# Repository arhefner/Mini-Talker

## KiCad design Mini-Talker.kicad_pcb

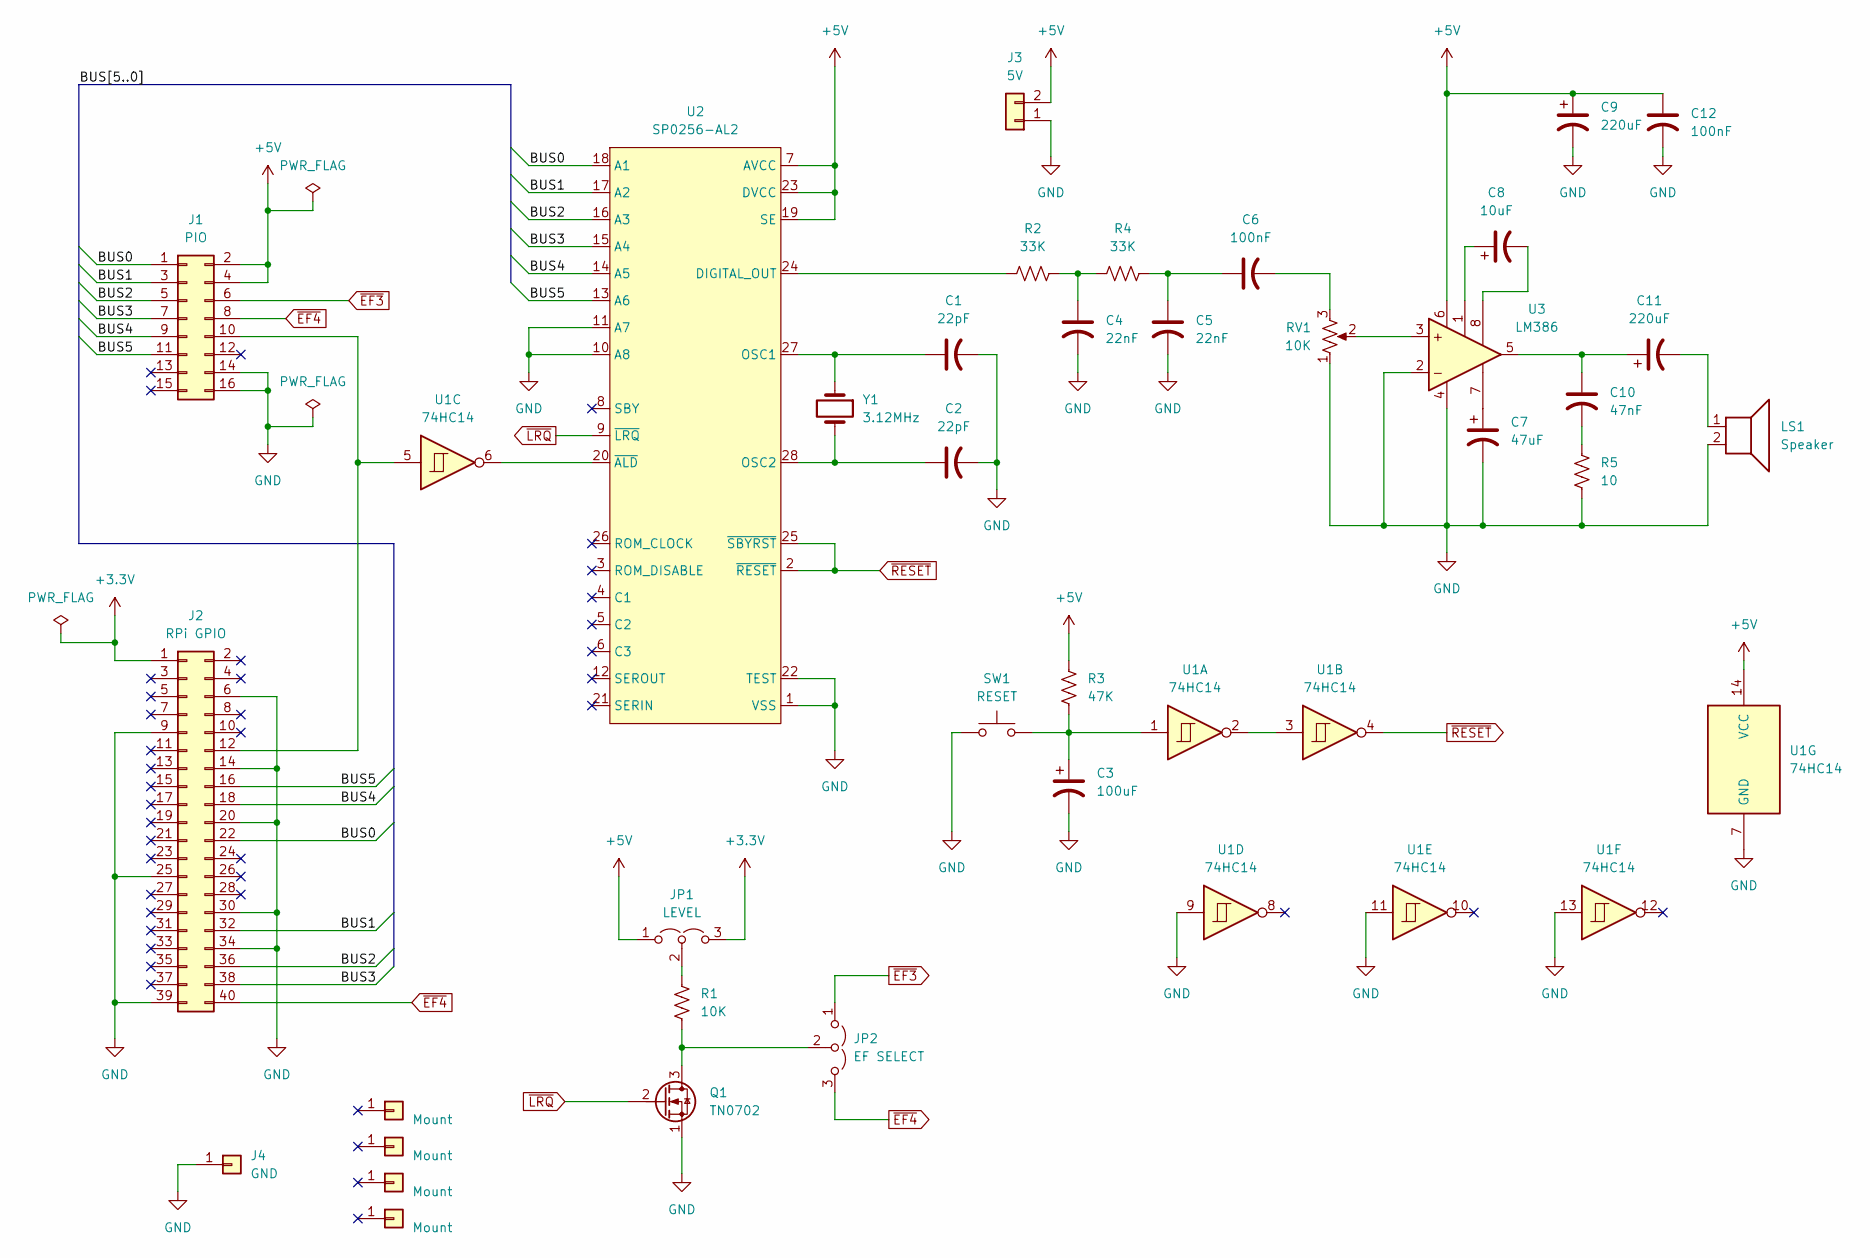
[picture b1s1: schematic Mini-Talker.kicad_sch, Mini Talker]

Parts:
C1, C2: 22pF; C_Disc_D5.0mm_W2.5mm_P2.50mm
C3: 100uF; CP_Radial_D5.0mm_P2.00mm
C4, C5: 22nF; C_Disc_D5.0mm_W2.5mm_P5.00mm
C6, C12: 100nF; C_Disc_D5.0mm_W2.5mm_P5.00mm
C7: 47uF; CP_Radial_D5.0mm_P2.00mm
C8: 10uF; CP_Radial_D4.0mm_P1.50mm
C9, C11: 220uF; CP_Radial_D6.3mm_P2.50mm
C10: 47nF; C_Disc_D5.0mm_W2.5mm_P5.00mm
J1: PIO; PinHeader_2x08_P2.54mm_Vertical
J2: RPi GPIO; PinHeader_2x20_P2.54mm_Vertical
J3: 5V; PinHeader_1x02_P2.54mm_Horizontal
J4: GND; SolderWire-0.75sqmm_1x01_D1.25mm_OD2.3mm
J5, J6, J7, J8: Mount; 1-Pin
JP1: LEVEL; PinHeader_1x03_P2.54mm_Vertical
JP2: EF SELECT; PinHeader_1x03_P2.54mm_Vertical
LS1: Speaker; TerminalBlock_Phoenix_MKDS-1,5-2-5.08_1x02_P5.08mm_Horizont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
Q1: TN0702; TO-92L
R1: 10K; R_Axial_DIN0207_L6.3mm_D2.5mm_P10.16mm_Horizontal
R2, R4: 33K; R_Axial_DIN0207_L6.3mm_D2.5mm_P10.16mm_Horizontal
R3: 47K; R_Axial_DIN0207_L6.3mm_D2.5mm_P10.16mm_Horizontal
R5: 10; R_Axial_DIN0207_L6.3mm_D2.5mm_P10.16mm_Horizontal
RV1: 10K; P160KN0QC20A10K
SW1: RESET; SW_PUSH_6mm_H4.3mm
U1: 74HC14; DIP-14_W7.62mm_Socket
U2: SP0256-AL2; DIP-28_W15.24mm_Socket
U3: LM386; DIP-8_W7.62mm_Socket
Y1: 3.12MHz; Crystal_HC49-U_Horizontal

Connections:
+3.3V: J2.1, JP1.3 (B)
+5V: C9.1, C12.1, J1.2, J1.4, J3.2, JP1.1 (A), R3.1, U1.14 (VCC), U2.7 (AVCC), U2.19 (SE), U2.23 (DVCC), U3.6 (V+)
/BUS0: J1.1, J2.22, U2.18 (A1)
/BUS1: J1.3, J2.32, U2.17 (A2)
/BUS2: J1.5, J2.36, U2.16 (A3)
/BUS3: J1.7, J2.38, U2.15 (A4)
/BUS4: J1.9, J2.18, U2.14 (A5)
/BUS5: J1.11, J2.16, U2.13 (A6)
GND: C1.2, C2.2, C3.2, C4.2, C5.2, C7.2, C9.2, C12.2, J1.14, J1.16, J2.6, J2.9, J2.14, J2.20, J2.25, J2.30, J2.34, J2.39, J3.1, J4.1, LS1.2, Q1.1 (S), R5.2, RV1.1, SW1.1, U1.7 (GND), U1.9, U1.11, U1.13, U2.1 (VSS), U2.10 (A8), U2.11 (A7), U2.22 (TEST), U3.2 (-), U3.4 (GND)
unnamed: C3.1, R3.2, SW1.2, U1.1
unnamed: C4.1, R2.1, R4.1
unnamed: C5.1, C6.1, R4.2
unnamed: C6.2, RV1.3 (1)
unnamed: C8.1, U3.1 (GAIN)
unnamed: C8.2, U3.8 (GAIN)
unnamed: C10.1, C11.1, U3.5
unnamed: C10.2, R5.1
unnamed: C11.2, LS1.1
unnamed: J1.10, J2.12, U1.5
unnamed: JP1.2 (C), R1.1
unnamed: JP2.2 (C), Q1.3 (D), R1.2
unnamed: U1.2, U1.3
unnamed: R2.2, U2.24 (DIGITAL_OUT)
unnamed: C1.1, U2.27 (OSC1), Y1.1
unnamed: C2.1, U2.28 (OSC2), Y1.2
unnamed: U1.6, U2.20 (~ALD)
unnamed: RV1.2, U3.3 (+)
unnamed: C7.1, U3.7 (BYPASS)
~EF3: J1.6, JP2.1 (A)
~EF4: J1.8, J2.40, JP2.3 (B)
~LRQ: Q1.2 (G), U2.9 (~LRQ)
~RESET: U1.4, U2.2 (~RESET), U2.25 (~SBYRST)

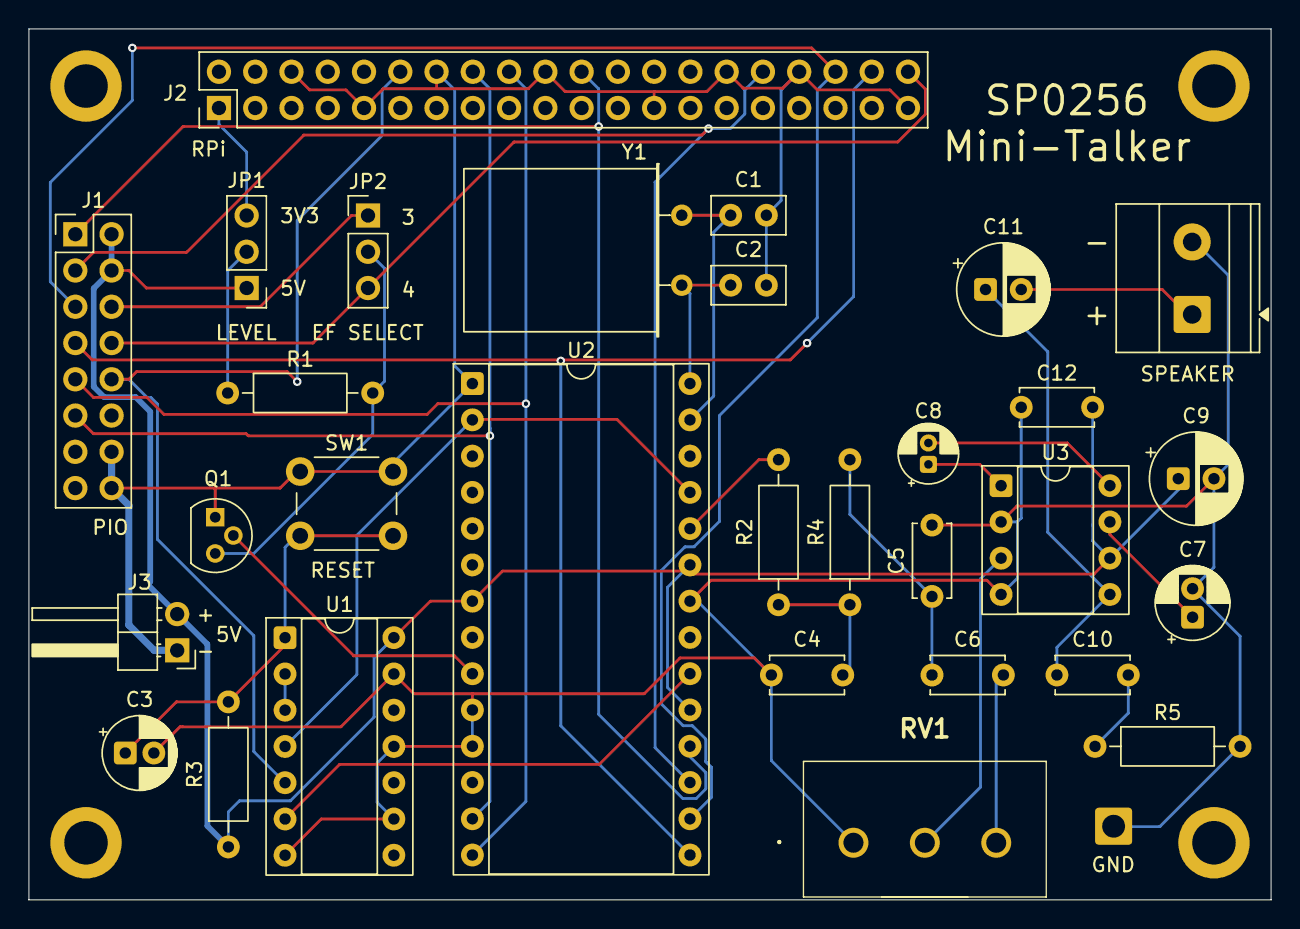
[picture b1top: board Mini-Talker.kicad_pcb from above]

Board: 2 copper layers, 87.0 x 61.0 mm, 35 parts (0 on the bottom side), 32 nets.

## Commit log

2025-09-08 Initial commit of design.
